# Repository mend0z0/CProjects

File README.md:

# CProjects
 In this repo, all projects will be done with C/CPP language

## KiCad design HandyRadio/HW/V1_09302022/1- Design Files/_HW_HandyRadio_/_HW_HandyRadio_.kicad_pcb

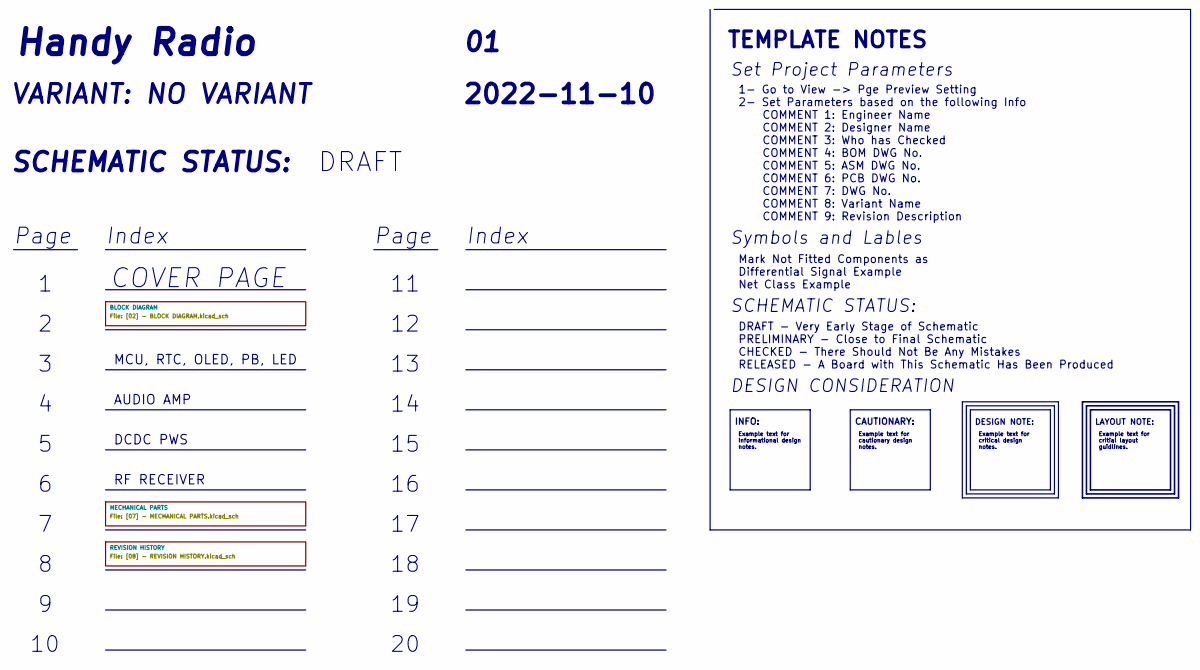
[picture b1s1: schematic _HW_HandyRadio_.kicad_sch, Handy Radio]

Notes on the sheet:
Page
Index
Example text for Informational design notes.
TEMPLATE NOTES
DRAFT
CAUTIONARY:
LAYOUT NOTE:
SCHEMATIC STATUS:
1- Go to View -> Pge Preview Setting 2- Set Parameters based on the following Info COMMENT 1: Engineer Name COMMENT 2: Designer Name COMMENT 3: Who has Checked COMMENT 4: BOM DWG No. COMMENT 5: ASM DWG No. COMMENT 6: PCB DWG No. COMMENT 7: DWG No. COMMENT 8: Variant Name COMMENT 9: Revision Descrip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
DCDC PWS
${REVISION}
Example text for cautionary design notes.
INFO:
DESIGN NOTE:
Example text for critical design notes.
VARIANT: ${COMMENT8}
Set Project Parameters
SCHEMATIC STATUS:
${ISSUE_DATE}
AUDIO AMP
DRAFT - Very Early Stage of Schematic PRELIMINARY - Close to Final Schematic CHECKED - There Should Not Be Any Mistakes RELEASED - A Board with This Schematic Has Been Produced
Example text for critial layout guidlines.
DESIGN CONSIDERATION
${TITLE}
MCU, RTC, OLED, PB, LED
Mark Not Fitted Components as Differential Signal Example Net Class Example
COVER PAGE
Symbols and Lables
RF RECEIVER

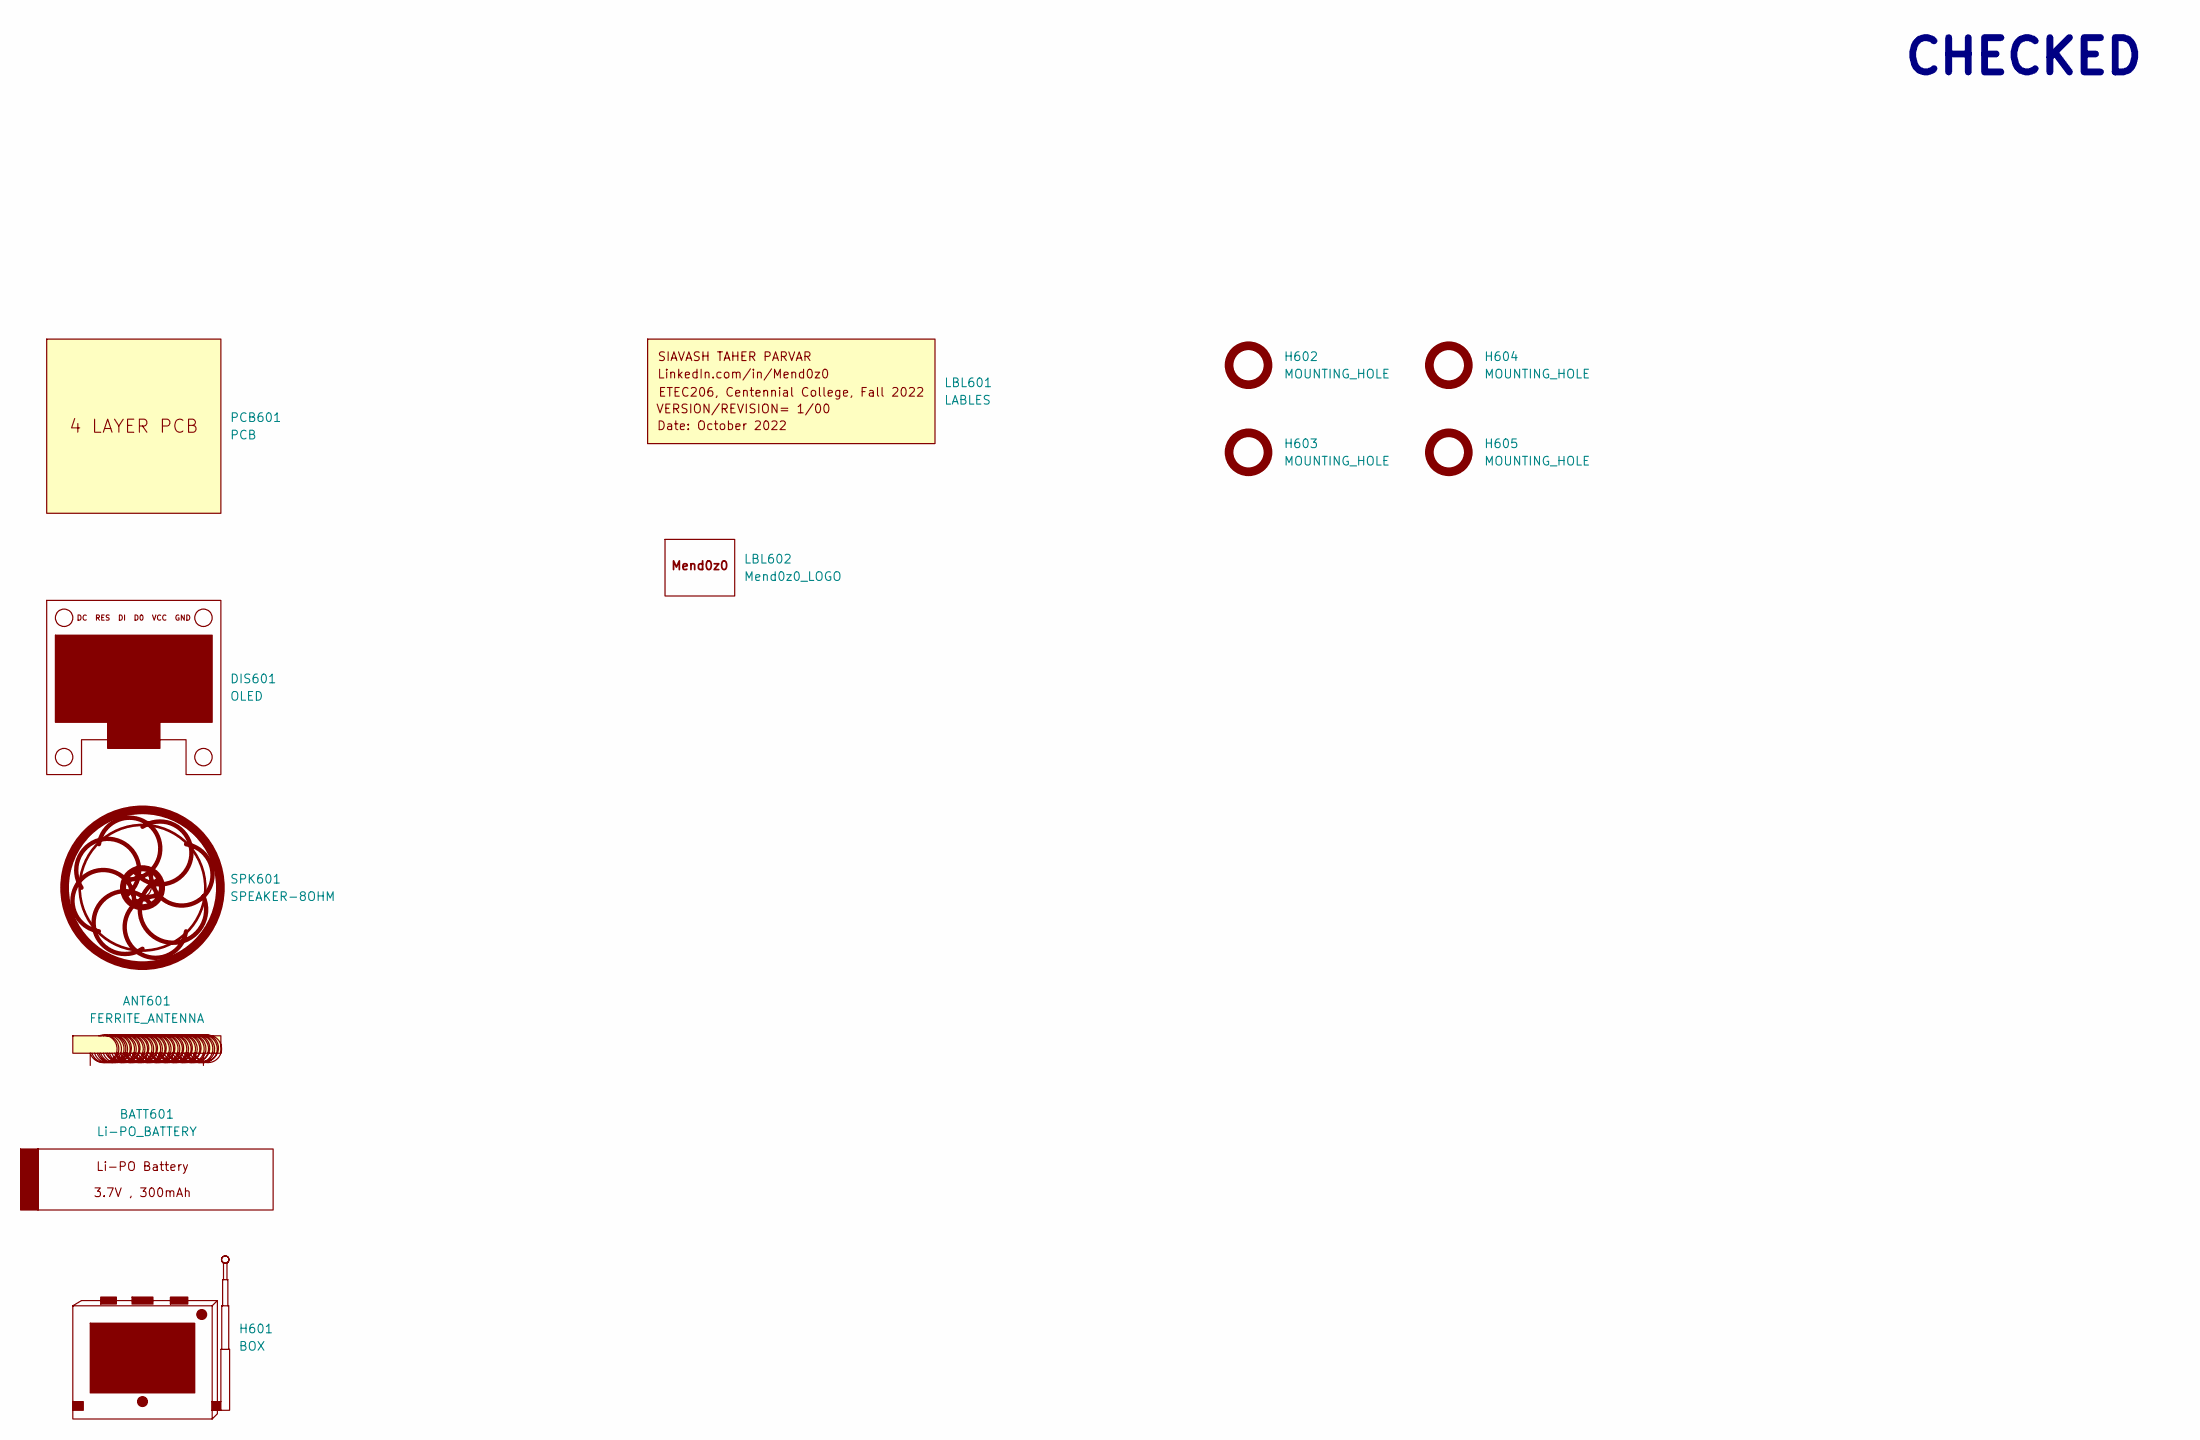
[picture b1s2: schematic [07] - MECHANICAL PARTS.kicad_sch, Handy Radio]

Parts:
ANT601: FERRITE_ANTENNA
BATT601: Li-PO_BATTERY
DIS601: OLED; OLED 1.3INCH
H601: BOX
H602, H603, H604, H605: MOUNTING_HOLE; MountingHole_3.2mm_M3
LBL601: LABLES
LBL602: Mend0z0_LOGO; Logo
PCB601: PCB
SPK601: SPEAKER-8OHM

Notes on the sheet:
CHECKED

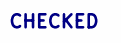
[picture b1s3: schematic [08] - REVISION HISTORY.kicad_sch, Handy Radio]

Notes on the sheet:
CHECKED

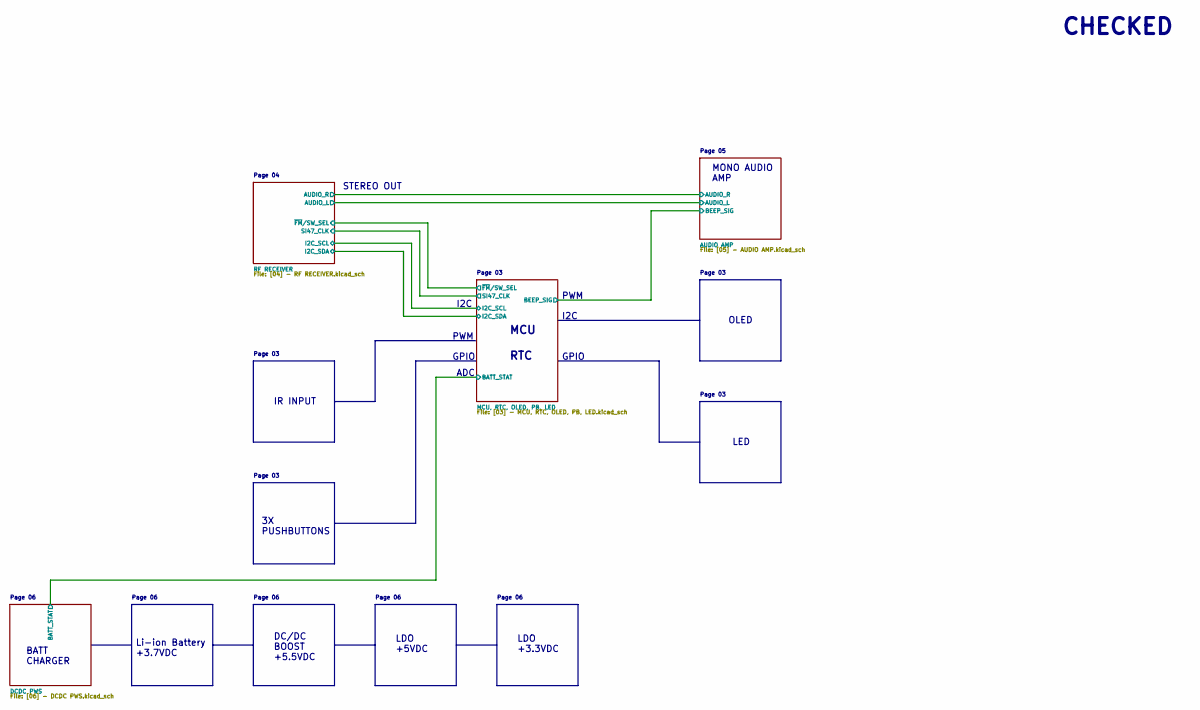
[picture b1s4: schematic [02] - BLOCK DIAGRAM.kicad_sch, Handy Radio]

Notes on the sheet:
IR INPUT
PWM
3X PUSHBUTTONS
Page 04
Page 03
DC/DC BOOST +5.5VDC
Page 06
I2C
GPIO
ADC
OLED
LDO +3.3VDC
MONO AUDIO AMP
MCU RTC
STEREO OUT
Li-ion Battery +3.7VDC
BATT CHARGER
LDO +5VDC
Page 05
CHECKED
LED

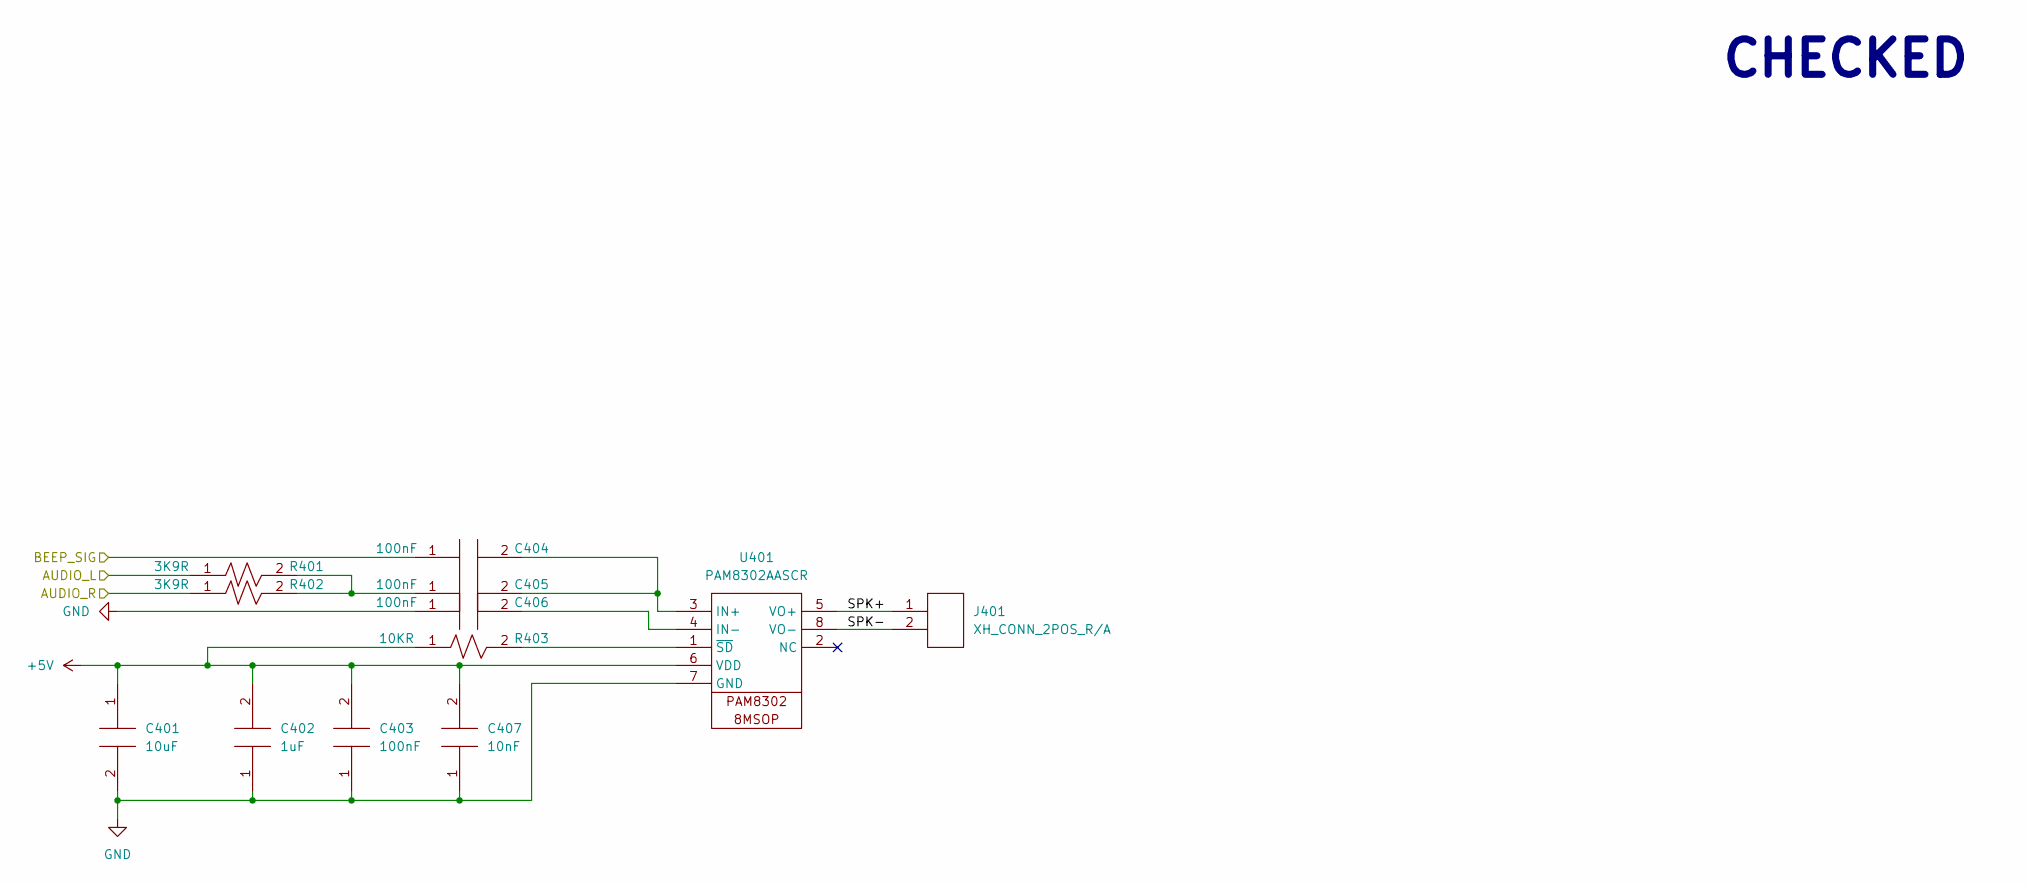
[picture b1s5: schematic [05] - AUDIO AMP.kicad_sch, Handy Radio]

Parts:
C401: 10uF; C_0805_2012Metric_Pad1.18x1.45mm_HandSolder
C402: 1uF; C_0805_2012Metric_Pad1.18x1.45mm_HandSolder
C403, C404, C405, C406: 100nF; C_0805_2012Metric_Pad1.18x1.45mm_HandSolder
C407: 10nF; C_0805_2012Metric_Pad1.18x1.45mm_HandSolder
J401: XH_CONN_2POS_R/A; JST_PH_S2B-PH-K_1x02_P2.00mm_Horizontal
R401, R402: 3K9R; R_0805_2012Metric_Pad1.20x1.40mm_HandSolder
R403: 10KR; R_0805_2012Metric_Pad1.20x1.40mm_HandSolder
U401: PAM8302AASCR; MSOP-8_3x3mm_P0.65mm

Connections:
+5V: C401.1, C402.2, C403.2, C407.2, R403.1, U401.6 (VDD); also elsewhere on the board
/BLOCK DIAGRAM/AUDIO AMP/AUDIO_L: R401.1; also elsewhere on the board
/BLOCK DIAGRAM/AUDIO AMP/AUDIO_R: R402.1; also elsewhere on the board
/BLOCK DIAGRAM/AUDIO AMP/SPK+: J401.1, U401.5 (VO+)
/BLOCK DIAGRAM/AUDIO AMP/SPK-: J401.2, U401.8 (VO-)
/BLOCK DIAGRAM/MCU, RTC, OLED, PB, LED/BEEP_OUPUT: C404.1; also elsewhere on the board
GND: C401.2, C402.1, C403.1, C406.1, C407.1, U401.7 (GND); also elsewhere on the board
unnamed: C404.2, C405.2, U401.3 (IN+)
unnamed: C405.1, R401.2, R402.2
unnamed: C406.2, U401.4 (IN-)
unnamed: R403.2, U401.1 (~SD)

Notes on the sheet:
CHECKED

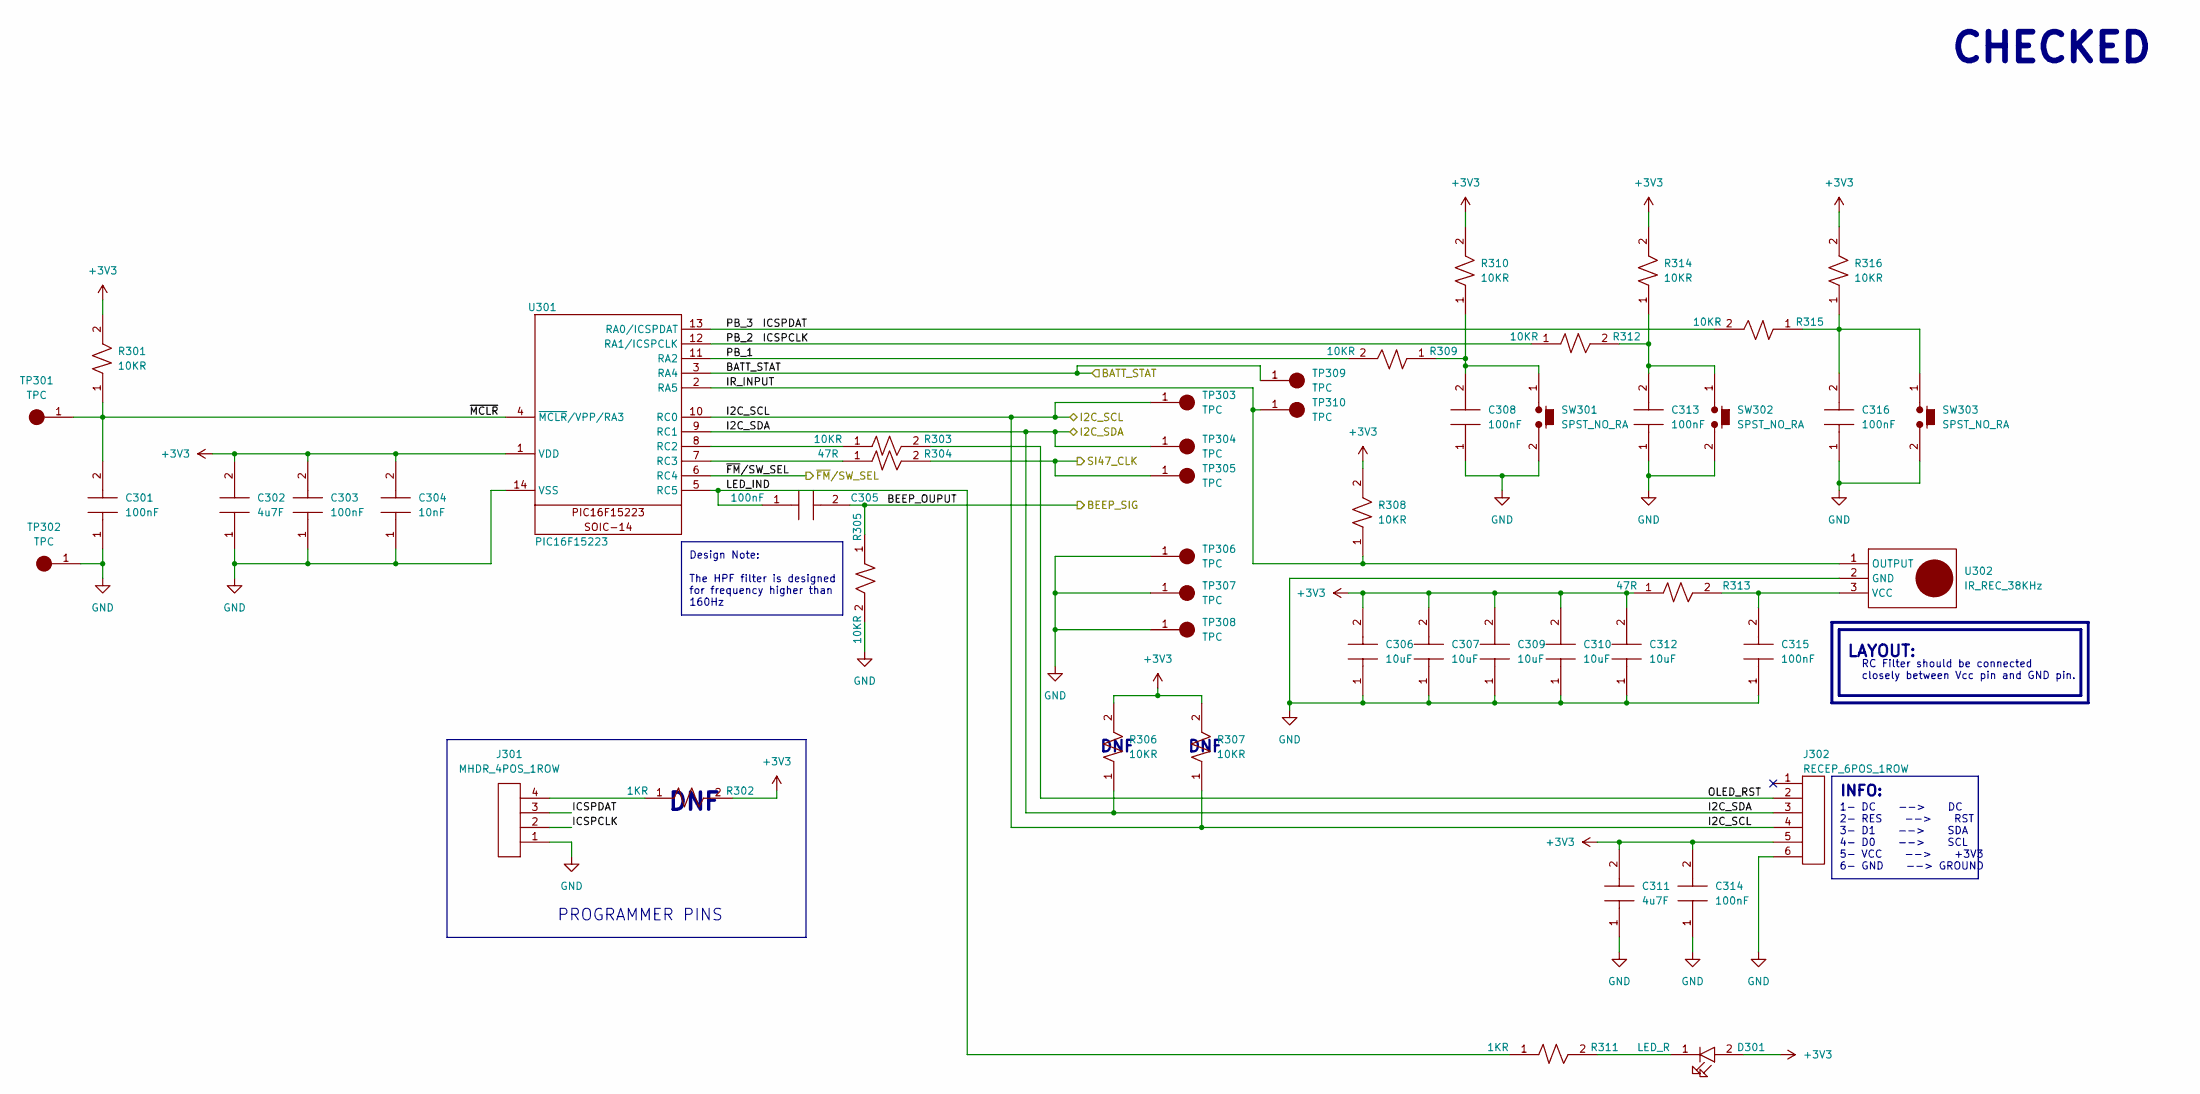
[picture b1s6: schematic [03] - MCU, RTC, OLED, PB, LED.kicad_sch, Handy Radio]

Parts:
C301, C303, C305, C308, C313, C314, C315, C316: 100nF; C_0805_2012Metric_Pad1.18x1.45mm_HandSolder
C302, C311: 4u7F; C_0805_2012Metric_Pad1.18x1.45mm_HandSolder
C304: 10nF; C_0805_2012Metric_Pad1.18x1.45mm_HandSolder
C306, C307, C309, C310, C312: 10uF; C_0805_2012Metric_Pad1.18x1.45mm_HandSolder
D301: LED_R; LED_D5.0mm
J301: MHDR_4POS_1ROW; PinHeader_1x04_P2.54mm_Vertical
J302: RECEP_6POS_1ROW; PinHeader_1x06_P2.54mm_Vertical
R301, R303, R305, R306, R307, R308, R309, R310, R312, R314, R315, R316: 10KR; R_0805_2012Metric_Pad1.20x1.40mm_HandSolder
R302, R311: 1KR; R_0805_2012Metric_Pad1.20x1.40mm_HandSolder
R304, R313: 47R; R_0805_2012Metric_Pad1.20x1.40mm_HandSolder
SW301, SW302, SW303: SPST_NO_RA; SW_Tact_SKHH_Angled
TP301, TP302, TP303, TP304, TP305, TP306, TP307, TP308, TP309, TP310: TPC; TestPoint_Pad_D1.5mm
U301: PIC16F15223; SO-14_3.9x8.65mm_P1.27mm
U302: IR_REC_38KHz; PinHeader_1x03_P2.54mm_Vertical

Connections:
+3V3: C302.2, C303.2, C304.2, C306.2, C307.2, C309.2, C310.2, C311.2, C312.2, C314.2, D301.2, J302.5, R301.2, R302.2, R306.2, R307.2, R308.2, R310.2, R313.1, R314.2, R316.2, U301.1 (VDD); also elsewhere on the board
/BLOCK DIAGRAM/MCU, RTC, OLED, PB, LED/BATT_STAT: TP309.1, U301.3 (RA4); also elsewhere on the board
/BLOCK DIAGRAM/MCU, RTC, OLED, PB, LED/BEEP_OUPUT: C305.2, R305.1; also elsewhere on the board
/BLOCK DIAGRAM/MCU, RTC, OLED, PB, LED/I2C_SCL: J302.4, R307.1, TP303.1, U301.10 (RC0); also elsewhere on the board
/BLOCK DIAGRAM/MCU, RTC, OLED, PB, LED/I2C_SDA: J302.3, R306.1, TP304.1, U301.9 (RC1); also elsewhere on the board
/BLOCK DIAGRAM/MCU, RTC, OLED, PB, LED/ICSPCLK: J301.2, R312.1, U301.12 (RA1/ICSPCLK)
/BLOCK DIAGRAM/MCU, RTC, OLED, PB, LED/ICSPDAT: J301.3, R315.2, U301.13 (RA0/ICSPDAT)
/BLOCK DIAGRAM/MCU, RTC, OLED, PB, LED/IR_INPUT: R308.1, TP310.1, U301.2 (RA5), U302.1 (OUTPUT)
/BLOCK DIAGRAM/MCU, RTC, OLED, PB, LED/LED_IND: C305.1, R311.1, U301.5 (RC5)
/BLOCK DIAGRAM/MCU, RTC, OLED, PB, LED/OLED_RST: J302.2, R303.2
/BLOCK DIAGRAM/MCU, RTC, OLED, PB, LED/PB_1: R309.2, U301.11 (RA2)
/BLOCK DIAGRAM/MCU, RTC, OLED, PB, LED/SI47_CLK: R304.2, TP305.1; also elsewhere on the board
/BLOCK DIAGRAM/MCU, RTC, OLED, PB, LED/~FM/SW_SEL: U301.6 (RC4); also elsewhere on the board
/BLOCK DIAGRAM/MCU, RTC, OLED, PB, LED/~MCLR: C301.2, R301.1, TP301.1, U301.4 (~MCLR/VPP/RA3)
GND: C301.1, C302.1, C303.1, C304.1, C306.1, C307.1, C308.1, C309.1, C310.1, C311.1, C312.1, C313.1, C314.1, C315.1, C316.1, J301.1, J302.6, R305.2, SW301.2, SW302.2, SW303.2, TP302.1, TP306.1, TP307.1, TP308.1, U301.14 (VSS), U302.2 (GND); also elsewhere on the board
unnamed: C308.2, R309.1, R310.1, SW301.1
unnamed: C313.2, R312.2, R314.1, SW302.1
unnamed: C315.2, R313.2, U302.3 (VCC)
unnamed: C316.2, R315.1, R316.1, SW303.1
unnamed: D301.1, R311.2
unnamed: J301.4, R302.1
unnamed: R303.1, U301.8 (RC2)
unnamed: R304.1, U301.7 (RC3)

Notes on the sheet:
PROGRAMMER PINS
1- DC --> DC 2- RES --> RST 3- D1 --> SDA 4- D0 --> SCL 5- VCC --> +3V3 6- GND --> GROUND
INFO:
DNF
Design Note: The HPF filter is designed for frequency higher than 160Hz
CHECKED
LAYOUT:
RC Filter should be connected closely between Vcc pin and GND pin.

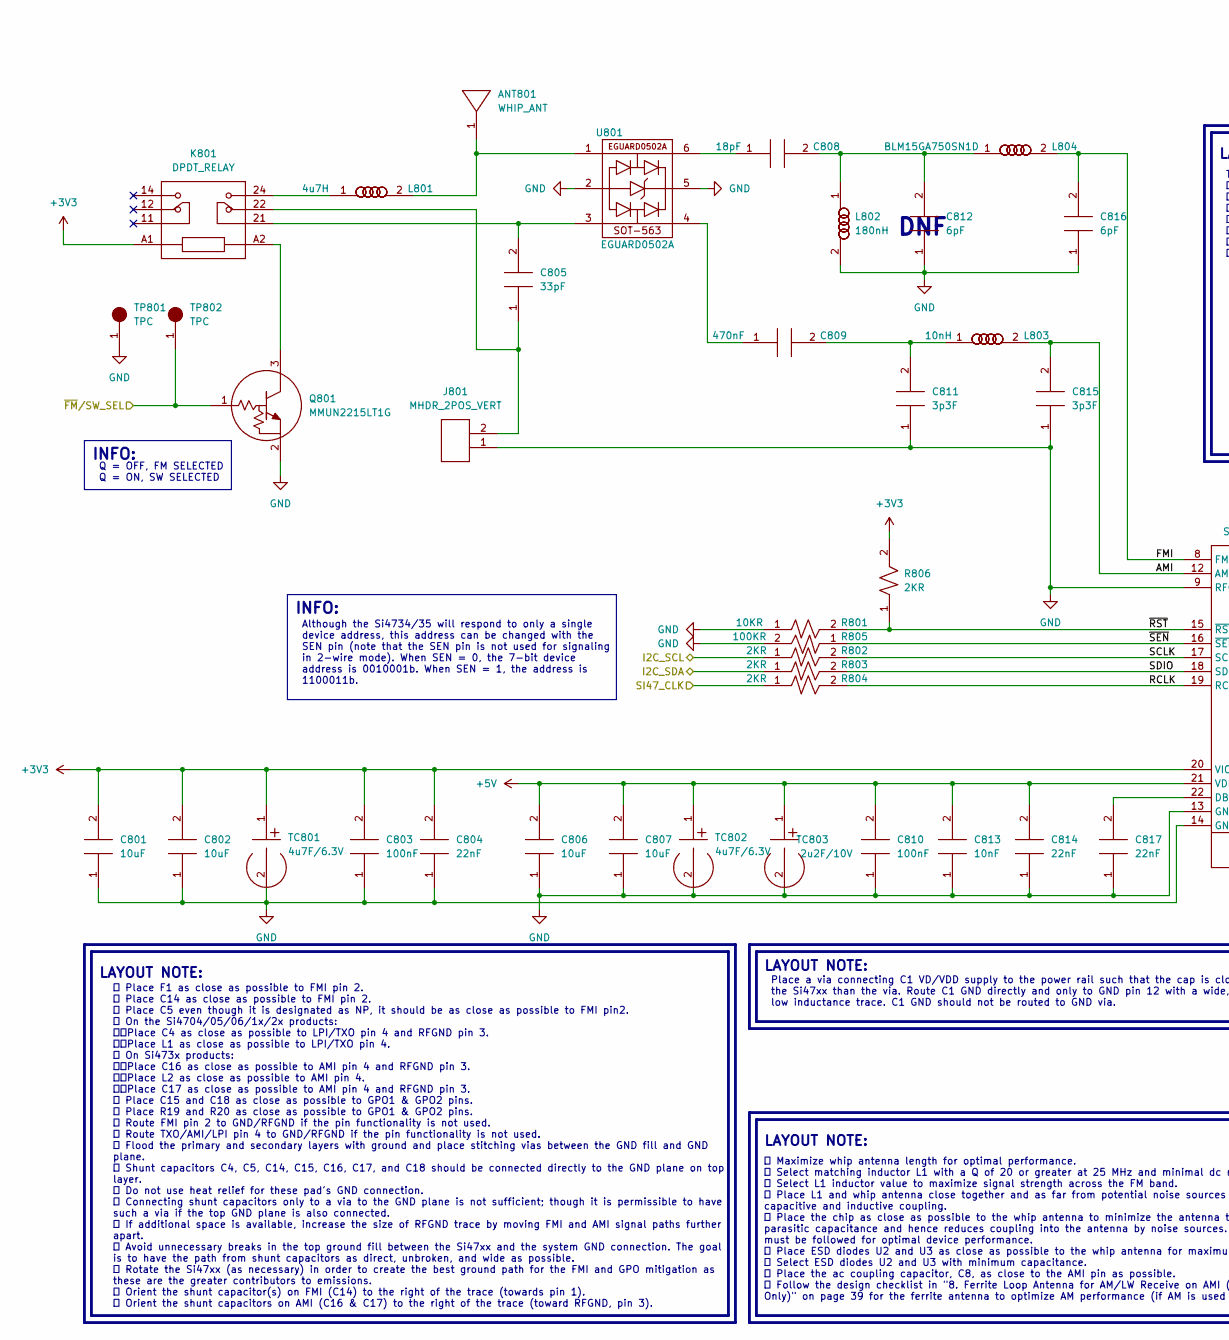
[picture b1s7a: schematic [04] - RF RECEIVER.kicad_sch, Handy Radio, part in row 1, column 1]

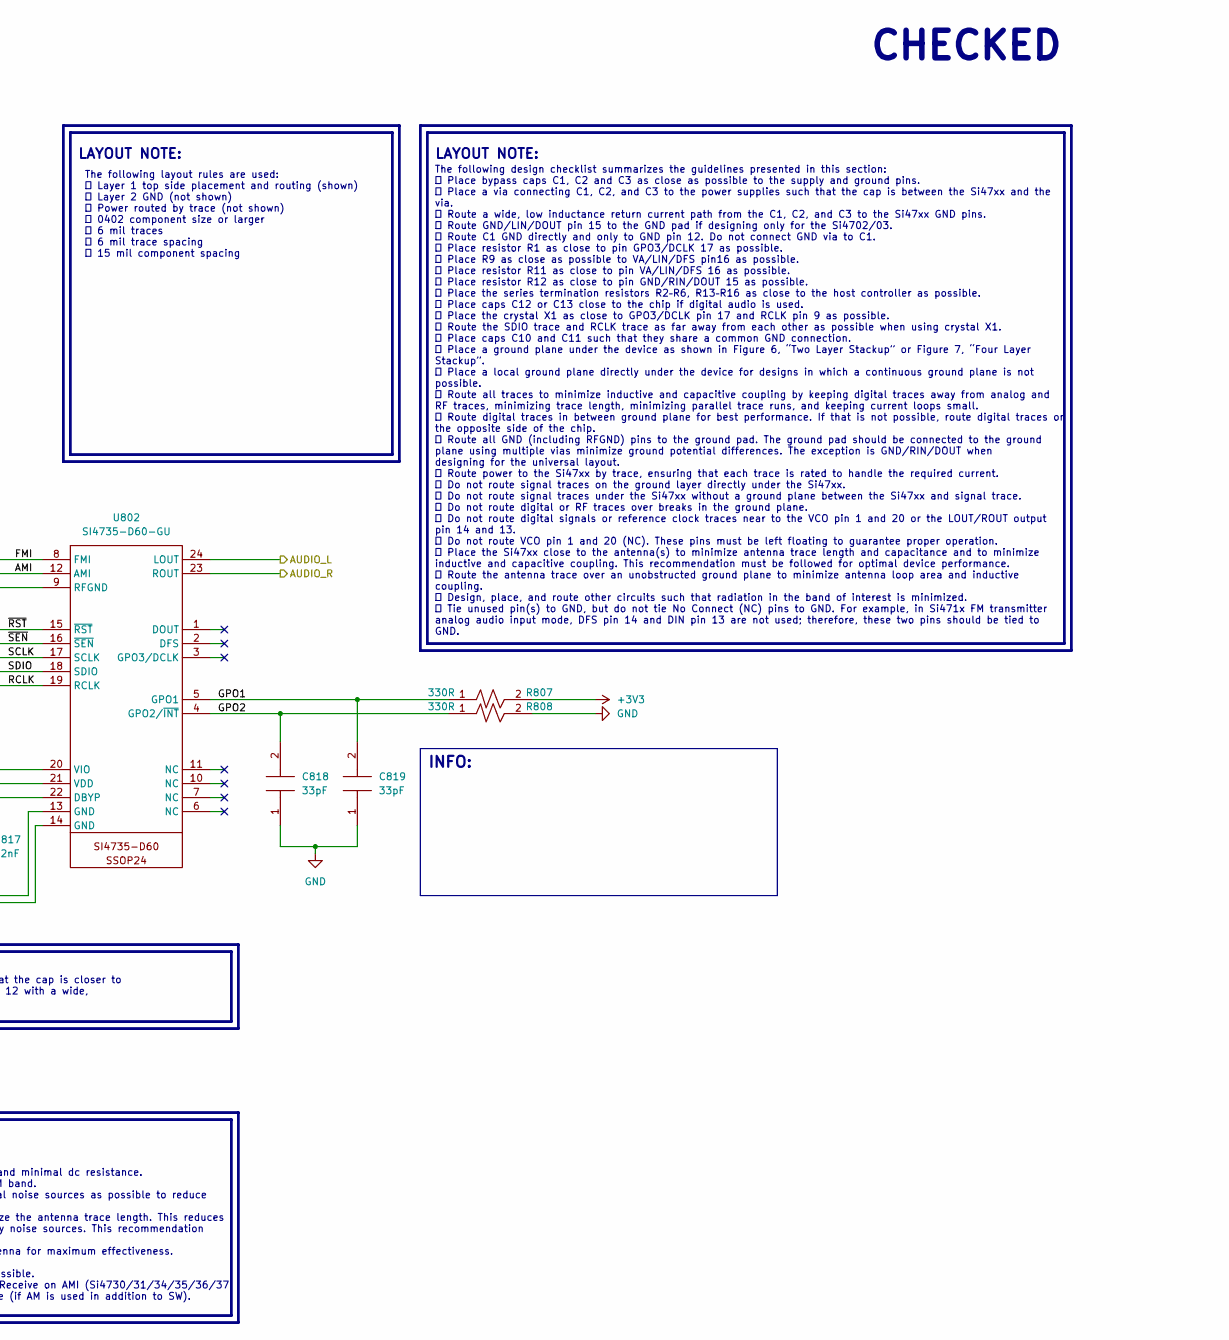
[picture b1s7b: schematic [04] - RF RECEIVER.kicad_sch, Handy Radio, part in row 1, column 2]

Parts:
ANT801: WHIP_ANT; MountingHole_3.2mm_M3_Pad_Via
C801, C802, C806, C807: 10uF; C_0805_2012Metric_Pad1.18x1.45mm_HandSolder
C803, C810: 100nF; C_0805_2012Metric_Pad1.18x1.45mm_HandSolder
C804, C814, C817: 22nF; C_0805_2012Metric_Pad1.18x1.45mm_HandSolder
C805, C818, C819: 33pF; C_0805_2012Metric_Pad1.18x1.45mm_HandSolder
C808: 18pF; C_0805_2012Metric_Pad1.18x1.45mm_HandSolder
C809: 470nF; C_0805_2012Metric_Pad1.18x1.45mm_HandSolder
C811, C815: 3p3F; C_0805_2012Metric_Pad1.18x1.45mm_HandSolder
C812, C816: 6pF; C_0805_2012Metric_Pad1.18x1.45mm_HandSolder
C813: 10nF; C_0805_2012Metric_Pad1.18x1.45mm_HandSolder
J801: MHDR_2POS_VERT; PinHeader_1x02_P2.54mm_Vertical
K801: DPDT_RELAY; Relay_DPDT_Finder_30.22
L801: 4u7H; L_0805_2012Metric_Pad1.05x1.20mm_HandSolder
L802: 180nH; L_0603_1608Metric_Pad1.05x0.95mm_HandSolder
L803: 10nH; L_0603_1608Metric_Pad1.05x0.95mm_HandSolder
L804: BLM15GA750SN1D; L_0402_1005Metric_Pad0.77x0.64mm_HandSolder
Q801: MMUN2215LT1G; SOT-23
R801: 10KR; R_0805_2012Metric_Pad1.20x1.40mm_HandSolder
R802, R803, R804, R806: 2KR; R_0805_2012Metric_Pad1.20x1.40mm_HandSolder
R805: 100KR; R_0805_2012Metric_Pad1.20x1.40mm_HandSolder
R807, R808: 330R; R_0805_2012Metric_Pad1.20x1.40mm_HandSolder
TC801, TC802: 4u7F/6.3V; CP_EIA-2012-12_Kemet-R_Pad1.30x1.05mm_HandSolder
TC803: 2u2F/10V; CP_EIA-2012-12_Kemet-R_Pad1.30x1.05mm_HandSolder
TP801, TP802: TPC; TestPoint_Pad_D1.5mm
U801: EGUARD0502A; SOT-563
U802: SI4735-D60-GU; SSOP-24_3.9x8.7mm_P0.635mm

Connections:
+3V3: C801.2, C802.2, C803.2, C804.2, K801.A1, R806.2, R807.2, TC801.1, U802.20 (VIO); also elsewhere on the board
+5V: C806.2, C807.2, C810.2, C813.2, C814.2, TC802.1, TC803.1, U802.21 (VDD); also elsewhere on the board
/BLOCK DIAGRAM/AUDIO AMP/AUDIO_L: U802.24 (LOUT); also elsewhere on the board
/BLOCK DIAGRAM/AUDIO AMP/AUDIO_R: U802.23 (ROUT); also elsewhere on the board
/BLOCK DIAGRAM/MCU, RTC, OLED, PB, LED/I2C_SCL: R802.1; also elsewhere on the board
/BLOCK DIAGRAM/MCU, RTC, OLED, PB, LED/I2C_SDA: R803.1; also elsewhere on the board
/BLOCK DIAGRAM/MCU, RTC, OLED, PB, LED/SI47_CLK: R804.1; also elsewhere on the board
/BLOCK DIAGRAM/MCU, RTC, OLED, PB, LED/~FM/SW_SEL: Q801.1, TP802.1; also elsewhere on the board
/BLOCK DIAGRAM/RF RECEIVER/AMI: C815.2, L803.2, U802.12 (AMI)
/BLOCK DIAGRAM/RF RECEIVER/FMI: C816.2, L804.2, U802.8 (FMI)
/BLOCK DIAGRAM/RF RECEIVER/GPO1: C819.2, R807.1, U802.5 (GPO1)
/BLOCK DIAGRAM/RF RECEIVER/GPO2: C818.2, R808.1, U802.4 (GPO2/~INT)
/BLOCK DIAGRAM/RF RECEIVER/RCLK: R804.2, U802.19 (RCLK)
/BLOCK DIAGRAM/RF RECEIVER/SCLK: R802.2, U802.17 (SCLK)
/BLOCK DIAGRAM/RF RECEIVER/SDIO: R803.2, U802.18 (SDIO)
/BLOCK DIAGRAM/RF RECEIVER/~RST: R801.2, R806.1, U802.15 (~RST)
/BLOCK DIAGRAM/RF RECEIVER/~SEN: R805.1, U802.16 (~SEN)
GND: C801.1, C802.1, C803.1, C804.1, C806.1, C807.1, C810.1, C811.1, C812.1, C813.1, C814.1, C815.1, C816.1, C817.1, C818.1, C819.1, J801.1, L802.2, Q801.2, R801.1, R805.2, R808.2, TC801.2, TC802.2, TC803.2, TP801.1, U801.2, U801.5, U802.9 (RFGND), U802.13 (GND), U802.14 (GND); also elsewhere on the board
unnamed: ANT801.1, L801.2, U801.1
unnamed: C805.1, J801.2, K801.22
unnamed: C805.2, K801.21, U801.3
unnamed: C808.1, U801.6
unnamed: C808.2, C812.2, L802.1, L804.1
unnamed: C809.1, U801.4
unnamed: C809.2, C811.2, L803.1
unnamed: C817.2, U802.22 (DBYP)
unnamed: K801.24, L801.1
unnamed: K801.A2, Q801.3

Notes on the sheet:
INFO:
The following design checklist summarizes the guidelines presented in this section:  Place bypass caps C1, C2 and C3 as close as possible to the supply and ground pins.  Place a via connecting C1, C2, and C3 to the power supplies such that the cap is between the Si47xx and the via.  Route a wide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
The following layout rules are used:  Layer 1 top side placement and routing (shown)  Layer 2 GND (not shown)  Power routed by trace (not shown)  0402 component size or larger  6 mil traces  6 mil trace spacing  15 mil component spacing
Although the Si4734/35 will respond to only a single device address, this address can be changed with the SEN pin (note that the SEN pin is not used for signaling in 2-wire mode). When SEN = 0, the 7-bit device address is 0010001b. When SEN = 1, the address is 1100011b.
LAYOUT NOTE:
DNF
Q = OFF, FM SELECTED Q = ON, SW SELECTED
CHECKED
Place a via connecting C1 VD/VDD supply to the power rail such that the cap is closer to the Si47xx than the via. Route C1 GND directly and only to GND pin 12 with a wide, low inductance trace. C1 GND should not be routed to GND via.
 Place F1 as close as possible to FMI pin 2.  Place C14 as close as possible to FMI pin 2.  Place C5 even though it is designated as NP, it should be as close as possible to FMI pin2.  On the Si4704/05/06/1x/2x products: Place C4 as close as possible to LPI/TXO pin 4 and RFGND pin 3. Place 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
 Maximize whip antenna length for optimal performance.  Select matching inductor L1 with a Q of 20 or greater at 25 MHz and minimal dc resistance.  Select L1 inductor value to maximize signal strength across the FM band.  Place L1 and whip antenna close together and as far from potential noise 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

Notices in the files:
HandyRadio/HW/V1_09302022/1- Design Files/_HW_HandyRadio_/_HW_HandyRadio_.kicad_pcb:
(C) 2022 Siavash Taher Parvar ALL RIGHTS RESERVED
